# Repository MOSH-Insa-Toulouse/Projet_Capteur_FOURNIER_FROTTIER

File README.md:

# Projet_Capteur_FOURNIER_FROTTIER
Acquisition chain to characterize graphite sensor

# Sommaire

1) Introduction
2) Code Arduino
3) Shield PCB
4) APK
5) Banc de test et mesures
6) Pistes d'amélioration
7) Contacts

# Introduction

Le capteur de déformation est constitué d'un morceau de papier sur lequel on dépose du graphite en coloriant avec un crayon à papier. Les particules de graphite forment alors un système granulaire. Ainsi lorsqu'on plie légèrement le papier, les particules s'éloignent ou se rapprochent les unes des autres (dépend du sens dans lequel on le plie). Dans le cas d'une compression (rapprochement des particules) l'effet tunnel fait qu'il y a plus d'électrons qui arrivent à passer d'une particule à une autre. Dans le cas d'une extension (éloignement des particules) c'est l'inverse qui se produit. Ainsi dans un cas la résistance diminue et dans l'autre cas elle augmente. Nous pouvons mesurer cette variation de résistance en mesurant la variation de courant. Ce capteur étant passif, il faut le conditionner. Pour cela nous introduisons un circuit transimpédance qui amplifie le courant mesuré et le convertit en tension. C'est cette tension qui est ensuite lue par l'entrée analogique de la carte Arduino.

# Code Arduino

Le code Arduino réalise la lecture analogique du signal amplifié sur l'entrée analogique A0 et convertit les valeurs analogiques en valeurs numériques (octets). Il permet également l'envoie des données octet par octet au module Bluetooth HC05. Sachant que ces données sont ensuite transmises par Bluetooth à l'APK, nous avons pris soin d'imposer la fréquence d'envoie des données (envoie d'un octet toutes les 200 ms, fréquence correspondant à celle de la clock de l'APK). Ainsi chaque octet envoyé est directement lu par l'APK sans delay. Ce code réalise aussi la communication avec l'écran OLED. Notez que pour cela il vous faut ajouter les librairies suivantes à votre code : Adafruit_GFX.h et Adafruit_SSD1306.h. Vous aurez aussi besoin de l'adresse d l'OLED (ici 0x3C). Notre fonction void LED() gère l'affichage de la tension Vadc en Volt (lue sur l'entrée A0) ainsi que le calcul et l'affichage de la résistance du capteur en MOhm.

# Shield PCB

Le shield a été réalisé sur le logiciel Kicad puis imprimé à l'Atelier d'électronique de l'INSA Toulouse. Nous y avons mis un circuit transimpédance afin d'amplifier le courant généré par le capteur et le convertir en tension. Nous y avons également pluggé le module Bluetooth HC05, l'écran OLED et un servomoteur (voir partie 5 Banc de test et mesures).

# APK

L'application Android a été réalisée via le site web MIT App Inventor. Elle communique avec le module Bluetooth de votre smartphone pour se connecter au module HC05 et recevoir des données. Pour cela, l'utilisateur n'a qu'à cliquer sur "Bluetooth" et choisir le module HC05 parmi la liste qui s'affiche. Une fois la connexion établie, l'application lit les données reçues par le smartphone et les affiche. On voit donc s'afficher à l'écran la valeur numérique de la tension Vadc en Volt et sa courbe sur un graphique. L'application calcule également la valeur de la résistance du capteur à partir de Vadc et des valeurs des résistances du montage transimpédance. La valeur numérique de la résistance est ensuite affichée sur l'écran.

# Banc de test et mesures

Afin d'échantillonner notre capteur, nous avons conçu un banc de test permettant d'obtenir la résistance du capteur pour un grand nombre de courbures différentes. Le banc a été conçu sous SoliWorks et imprimé en PLA à l'aide d'une imprimante 3D. En faisant tourner un servomoteur contrôlé par le programme Arduino, nous pouvons ainsi mesurer la résistance du capteur pour des angles de courbure précis et un grand nombre de fois. En laissant le moteur faire des va-et-vient plusieurs minutes nous nous retrouvons rapidement avec plusieurs milliers de points dans le Serial Monitor. Il suffit ensuite de copier ces données dans un nouveau fichier texte dans le même dossier que le programme Python. En modifiant le nom du fichier texte à traiter dans le code puis en l'exécutant on obtient un nuage de point des valeurs de résistance en fonction de l'angle de courbure. On observe que pour un certain intervalle d'angle, la résistance décroit linéairement avec la déformation (voir courbes dans la datasheet). A noter que le type de graphite (2H, 2B, HB ...) influence la variation de résistance.

# Limites et pistes d'améliorations

La principale limite de ce capteur est qu'il a une zone de non détérioration très restreinte (dépend du type de graphite mais généralement pas plus de 45°). Il va fonctionner pour de faibles déformations seulement. Si la déformation est trop importante, on endommage le capteur et la résistance ne varie plus linéairement. Un autre problème est qu'il est très difficile d'obtenir un signal stable. Même en maintenant la déformation constante, la résistance varie et on n'obtient jamais les mêmes valeurs d'une acquisition à une autre. C'est pour cette raison que nous avons fait un grand nombre de mesures. Le capteur est trop sensible et le courant mesuré dépend de trop de paramètres (l'expérimentateur, l'épaisseur de graphite, l'humidité, la pression, le contact des broches métalliques ...). Enfin on est limité par la résistance de gain du montage transimpédance. Pour certains types de graphite, le signal observé est trop faible, alors que pour d'autres, il sature. Une piste d'amélioration serait de mettre un connecteur sur le shield à la place de la résistance de gain, afin de pouvoir changer facilement la résistance et ainsi adapter le rapport d'amplification.

# Contacts

Ce projet a été réalisé par 2 étudiants de département Génie Physique de l'INSA Toulouse :
Théo Frottier : tfrottie@etud.insa-toulouse.fr
Tom Fournier : tfournie@etud.insa-toulouse.fr

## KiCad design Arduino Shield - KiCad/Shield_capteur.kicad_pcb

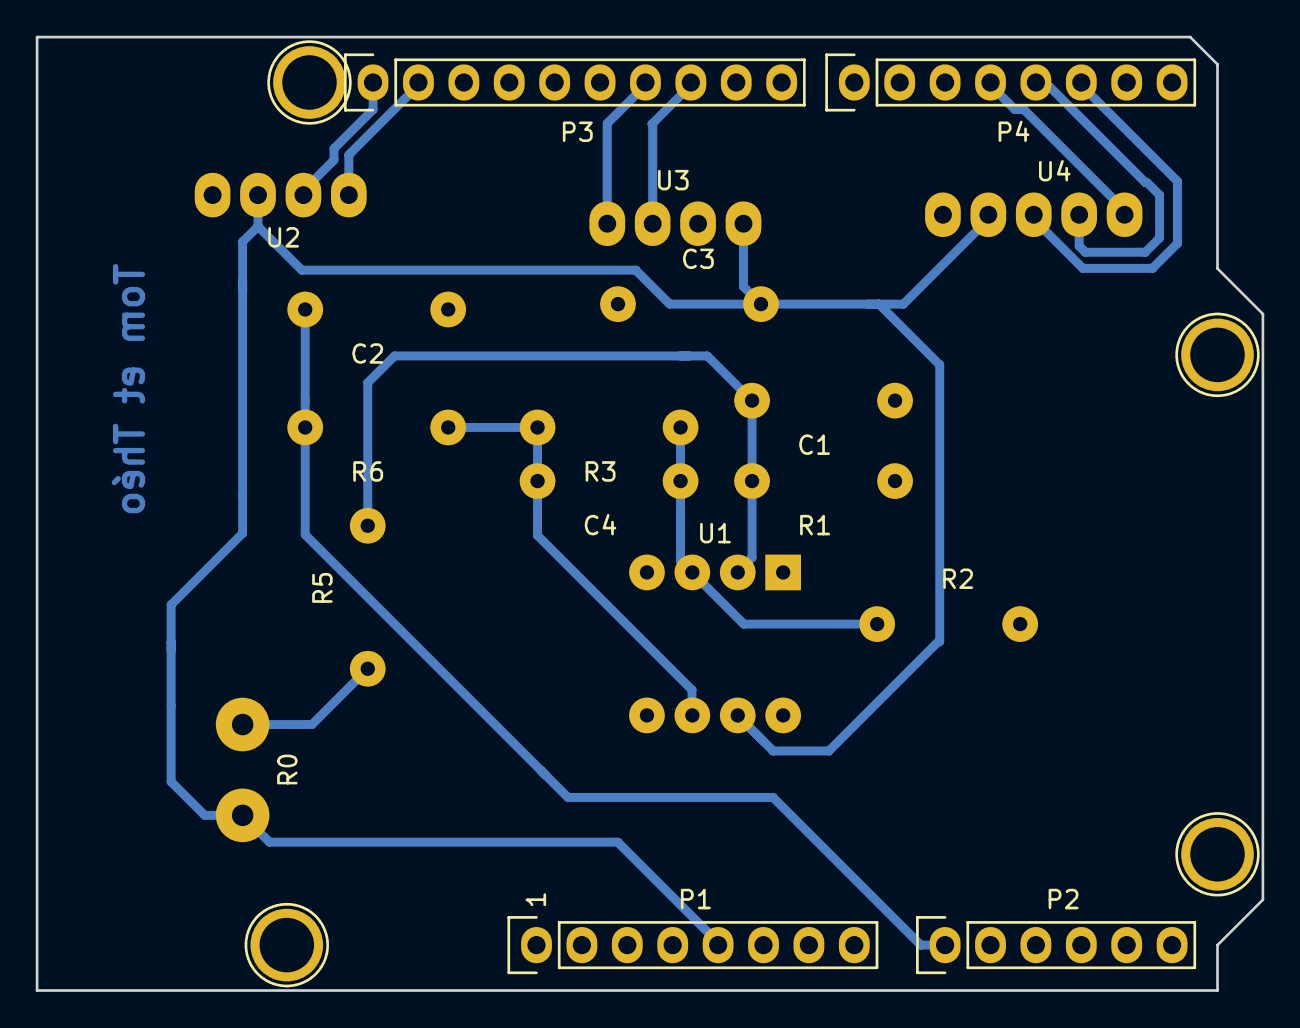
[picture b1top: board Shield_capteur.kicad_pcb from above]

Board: 2 copper layers, 68.6 x 53.3 mm, 22 parts (0 on the bottom side), 14 nets.

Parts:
C1, C2: 100N; Composant
C3: 100n; Composant
C4: 1µ; Composant
P1: Power; Socket_Strip_Arduino_1x08
P2: Analog; Socket_Strip_Arduino_1x06
P3: Digital; Socket_Strip_Arduino_1x10
P4: Digital; Socket_Strip_Arduino_1x08
P5, P6, P7, P8: CONN_01X01; Arduino_1pin
R0: Rsensor; Sensor
R1, R3: 100K; Composant
R2: 1K; Composant
R5: 10K; Composant
R6: 1k; Composant
U1: LT1050; Microcontroler
U2: OLED
U3: HC05; Bluetooth
U4: encodeur; Encodeur

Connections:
+5V: C3.1, P1.5, R0.1, U1.7, U2.2, U3.1, U4.4
ADC: C2.1, P2.1, R6.1
CLK: P4.4, U4.1
DATA: P4.5, U4.2
GND: C1.2, C2.2, C3.2, P1.6, P1.7, P3.4, R1.2, R2.1, U1.4, U2.1, U3.2, U4.5
IN+: C1.1, R1.1, R5.1, U1.3
IN-: C4.2, R2.2, R3.2, U1.2
unnamed: C4.1, R3.1, R6.2, U1.6
unnamed: R0.2, R5.2
RX: P3.8, U3.3
SDA: P3.2, U2.4
SDK: P3.1, U2.3
SWITCH: P4.6, U4.3
TX: P3.7, U3.4

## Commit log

2021-04-29 Premier essaie
